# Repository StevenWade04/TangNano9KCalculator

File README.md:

A simple calculator implemented as a finite state machine on a Tang Nano 9K.

Repo contains both parts, PCB design and Verilog code.

PCB:

Simple design in KICAD for through-hole soldering. A parts.txt file describes the correct components to be used for assembly.
The PCB is simple, and has several flaws. 

The through-holes for the headers are smaller than commonly available retail parts. 
The board has aesthetic issues.
The use of pull up resistors is likely not necessary with the Tang Nano 9k, and is simply a holdover from early work on the project.

Ideally these issues would be revised in a later iteration, potentially also making the board smaller, thus cheaper to print.

VERILOG:

Written with the intention of building and programming using LushayLabs IDE. In that enviroment the verilog code successfully is built and uploaded to the tang nano board It has not been tested directly using with Yosys's OSS Cad Suite, which the LushayLabs IDE directly uses.

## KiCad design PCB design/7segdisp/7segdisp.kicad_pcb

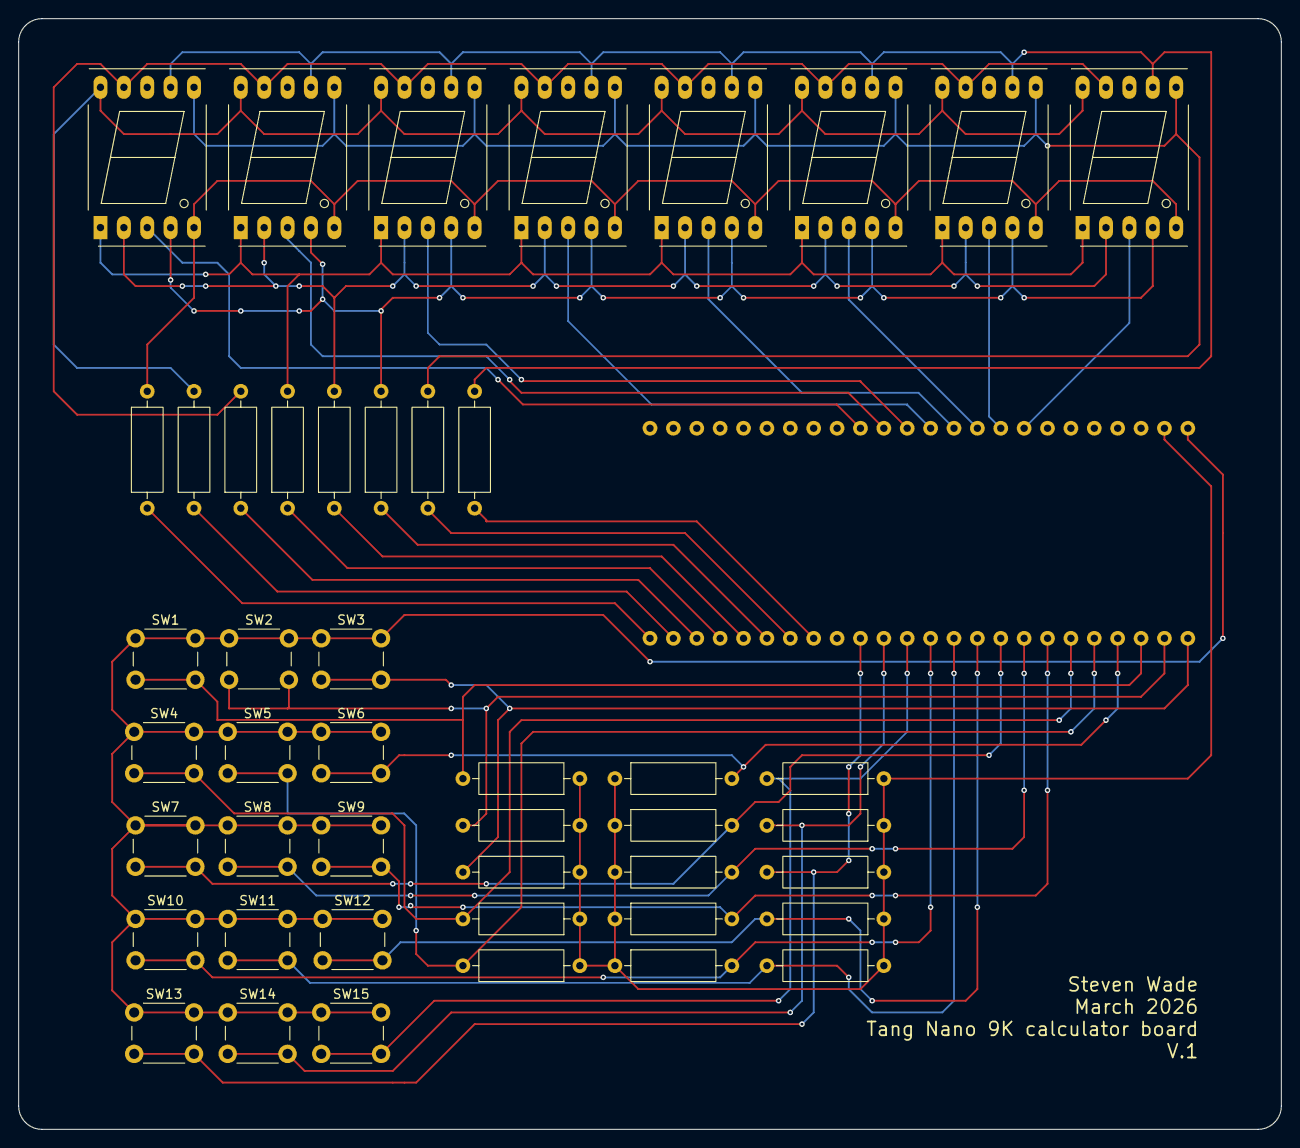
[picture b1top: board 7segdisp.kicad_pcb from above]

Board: 2 copper layers, 137.2 x 120.6 mm, 47 parts (0 on the bottom side), 41 nets.

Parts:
R1, R2, R3, R4, R5, R6, R7, R8, R9, R10, R11, R12, R13, R14, R15, R16, R17, R18, R19, R20, R21, R22, R24: R; R_Axial_DIN0309_L9.0mm_D3.2mm_P12.70mm_Horizontal
SW1, SW2, SW3, SW4, SW5, SW6, SW7, SW8, SW9, SW10, SW11, SW12, SW13, SW14, SW15: SW_Push; SW_PUSH_6mm
U1: TangNano9K
U2, U3, U4, U5, U6, U7, U8, U9: D1X8K-14BL; 7SegmentLED_LTS6760_LTS6780

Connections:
unnamed: R1.2, SW1.2, U1.22 (IOR13A)
unnamed: R6.2, SW6.2, U1.21 (IOR13A)
unnamed: SW1.1, SW2.1, SW3.1, SW4.1, SW5.1, SW6.1, SW7.1, SW8.1, SW9.1, SW10.1, SW11.1, SW12.1, SW13.1, SW14.1, SW15.1, U1.48 (3V3)
unnamed: R1.1, R2.1, R3.1, R4.1, R5.1, R6.1, R7.1, R8.1, R9.1, R10.1, R11.1, R12.1, R13.1, R14.1, R15.1, U1.47 (GND)
unnamed: R20.1, U1.5 (IOB8A)
unnamed: R21.1, U1.6 (IOB8B)
unnamed: R22.1, U1.7 (IOB11A)
unnamed: R24.1, U1.8 (IOB11B)
unnamed: R13.2, SW13.2, U1.10 (IOB13B)
unnamed: R14.2, SW14.2, U1.11 (IOB23A)
unnamed: R15.2, SW15.2, U1.12 (IOB23B)
unnamed: R11.2, SW11.2, U1.14 (IOB29A)
unnamed: R18.1, U1.3 (IOB29B)
unnamed: R17.1, U1.2 (IOB31A)
unnamed: R16.1, U1.1 (IOB31B)
unnamed: R19.1, U1.4 (IOB33A)
unnamed: R10.2, SW10.2, U1.13 (IOB33B)
unnamed: R12.2, SW12.2, U1.15 (IOB41A)
unnamed: R7.2, SW7.2, U1.16 (IOB41B)
unnamed: R5.2, SW5.2, U1.20 (IOR14B)
unnamed: R4.2, SW4.2, U1.19 (IOR15A)
unnamed: R9.2, SW9.2, U1.18 (IOR15B)
unnamed: R8.2, SW8.2, U1.17 (IOR17B)
unnamed: U1.34 (IOT37A), U2.3 (CC)
unnamed: U1.35 (IOT37B), U3.3 (CC)
unnamed: U1.36 (IOT38A), U4.3 (CC)
unnamed: U1.37 (IOT38B), U5.3 (CC)
unnamed: U1.38 (IOT39A), U6.3 (CC)
unnamed: U1.39 (IOT39B), U7.3 (CC)
unnamed: U1.40 (IOT41A), U8.3 (CC)
unnamed: U1.41 (IOT41B), U9.3 (CC)
unnamed: R3.2, SW3.2, U1.24 (IOT42A)
unnamed: R2.2, SW2.2, U1.23 (IOT42B)
unnamed: R24.2, U2.7 (A), U3.7 (A), U4.7 (A), U5.7 (A), U6.7 (A), U7.7 (A), U8.7 (A), U9.7 (A)
unnamed: R22.2, U2.6 (B), U3.6 (B), U4.6 (B), U5.6 (B), U6.6 (B), U7.6 (B), U8.6 (B), U9.6 (B)
unnamed: R21.2, U2.4 (C), U3.4 (C), U4.4 (C), U5.4 (C), U6.4 (C), U7.4 (C), U8.4 (C), U9.4 (C)
unnamed: R20.2, U2.2 (D), U3.2 (D), U4.2 (D), U5.2 (D), U6.2 (D), U7.2 (D), U8.2 (D), U9.2 (D)
unnamed: R16.2, U2.5 (DP), U3.5 (DP), U4.5 (DP), U5.5 (DP), U6.5 (DP), U7.5 (DP), U8.5 (DP), U9.5 (DP)
unnamed: R19.2, U2.1 (E), U3.1 (E), U4.1 (E), U5.1 (E), U6.1 (E), U7.1 (E), U8.1 (E), U9.1 (E)
unnamed: R18.2, U2.9 (F), U3.9 (F), U4.9 (F), U5.9 (F), U6.9 (F), U7.9 (F), U8.9 (F), U9.9 (F)
unnamed: R17.2, U2.10 (G), U3.10 (G), U4.10 (G), U5.10 (G), U6.10 (G), U7.10 (G), U8.10 (G), U9.10 (G)

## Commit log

2026-03-30 Included custom TangNano9k components
    Not included prior
2026-04-03 Commenting changes + changing readme format
    Minor commenting changes to sevenSegDriver, improving clarity on hex values not corresponding to digits.
    Readme format correction (.md rather than .txt)
2026-04-03 Renaming directory
2026-04-03 Updated numberConverter
    Changed number converter to use a more explicitly defines state machine.
    This was done to correct an error in BCD formatted value passthrough, where earlier iterations would cause either the BCD passthrough, or binary conversion to completely fail.
    Similarly to the previous iteration, it passes the testbench written for it, however this still requires testing on hardware prior to replacing the current NumberConverter.
2026-04-03 Optimization and bug fixes
    Corrected numberConverter.v to correctly pass through correctly formatted BCD digits. Previously this feature did not work. This was done by completely rewriting it to make the state machine clearer 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
    Additionally removes the hardcoded case for bin being equal to all ones setting output to the error code. The bcd is passed straight from the calculator state machine. (Keeping number converter gener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
    Verified working on hardware
2026-04-03 External operation handling outside of calcStateMachine
    This change puts the numerical operations into a seperate module, cleaning up the calculator state machine. Tested working.
2026-04-03 Implemented subtraction
    Subtraction implemented in functional manner. Still unhappy with how numbers are converted within operation.v.
    Correctly handles the overflow caused by negative numbers.
2026-04-09 addition and subtraction optimization
    Removed function from operation.v
    This function resulted in blowout in synthesis time.
    Now reduced.
    Tested and verified on hardware.
2026-04-09 Allow future mult, division support
    Allowed the state machine to handle going into multplication and division states. Not implemented still. Results in junk result if attempted.
2026-04-09 Code rewrite
    Removed very silly case statement.
2026-04-09 Multiplication
2026-04-09 Error revision
    Changed error display from
    Err
    to
    Error
